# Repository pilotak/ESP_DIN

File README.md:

# ESP8266 DIN mount relay
ESP8266 DIN mount relay *(DPDT@10A and SPST-NO@5A)* board with 433mHz RF receiver or generic input 230VAC or DC (based on jumper and resistor) and temperature sensor (DS18B20 or DHT22). Power supply is good old fashioned style transformer so no noise generated - **radioamateur friendly**. I2C/two pins are accesible on 2.54mm header, for you to extend capabilities.

Board features auto reset with set of GPIO0 LOW when uploading firmware via FTDI so you don't have to press any button to jump into program mode.

## Picture

*Please note that this is picture of v1.0 which in not available in this repo, I have updated the project to v1.1 which fixes some bugs and adds RC filter for relays*

## BOM
### Minimal components

| Qty | Component | Value | Package |
|:---:| --------- | ----- | ------- |
| 3 | Capacitor | 100n | 0805 |
| 1 | Capacitor | 100uF/16V |  Ø5mm, grid 2.032mm |
| 1 | Capacitor | 1000uF/16V | Ø10mm, grid 5mm |
| 2 | Capacitor | R463I24705001K | 18x5x11mm |
| 1 | Diode bridge | KBP307 | |
| 1 | Shottky diode | BAT54S | SOT23 |
| 2 | Diode | S1B | DO214AC (SMA) |
| 1 | Thermal fuse | 2A/115°C | |
| 1 | Fuse | TE5 500mA | TE5 |
| 1 | DPDT relay | 44.62.9.006.0000 | |
| 1 | SPST-NO relay | HF46F/005-HS1 | |
| 1 | LED | green | 3mm |
| 2 | Resistor | 1K | 0805 |
| 3 | Resistor | 4K7 | 0805 |
| 4 | Resistor | 10K | 0805 |
| 4 | Resistor | 160R | 2010 |
| 1 | Resistor | 820R | 0805 |
| 1 | Varistor | S07K275 | |
| 2 | NPN transistor | BC817 | SOT23 |
| 1 | Transformer | BV-EI-305-2050 EI30-1 | |
| 1 | Wifi module | ESP8266-12 | |
| 1 | LDO regulator | LM1117-3.3 | SOT223 |
| 3 | Screw terminal | KF301-5.08-2P | |
| 1 | Screw terminal | KF301-5.08-3P | |
| 1 | Screw terminal | KF350-3.5-2P | |
| 1 | Screw terminal | KF350-3.5-3P | |
| 1 | DIN case | Z100J PS | |

### If RF is required

| Qty | Component | Value | Package |
|:---:| --------- | ----- | ------- |
| 1 | RF reciever | RXB6 | |
| 1 | Capacitor | 100n | 0805 |
| 1 | Capacitor | 0.47uF | SMA |
| 1 | Capacitor | 10uF | SMA |
| 1 | Antenna conenctor | | SMA or u.fl connector |

### If IN is required

| Qty | Component | Value | Package |
|:---:| --------- | ----- | ------- |
| 1 | Diode | SL1M | SOD123 |
| 1 | Opto-coupler | TLP185 | SOP04 |
| 1 | Resistor | 0R | 2010 |
| 1 | Resistor | 200K | 2010 |
| 1 | Resistor | 10K | 0805 |
| 1 | Capacitor | 100n | 0805 |
| 1 | Capacitor | 100uF/16V |  Ø5mm, grid 2.032mm |

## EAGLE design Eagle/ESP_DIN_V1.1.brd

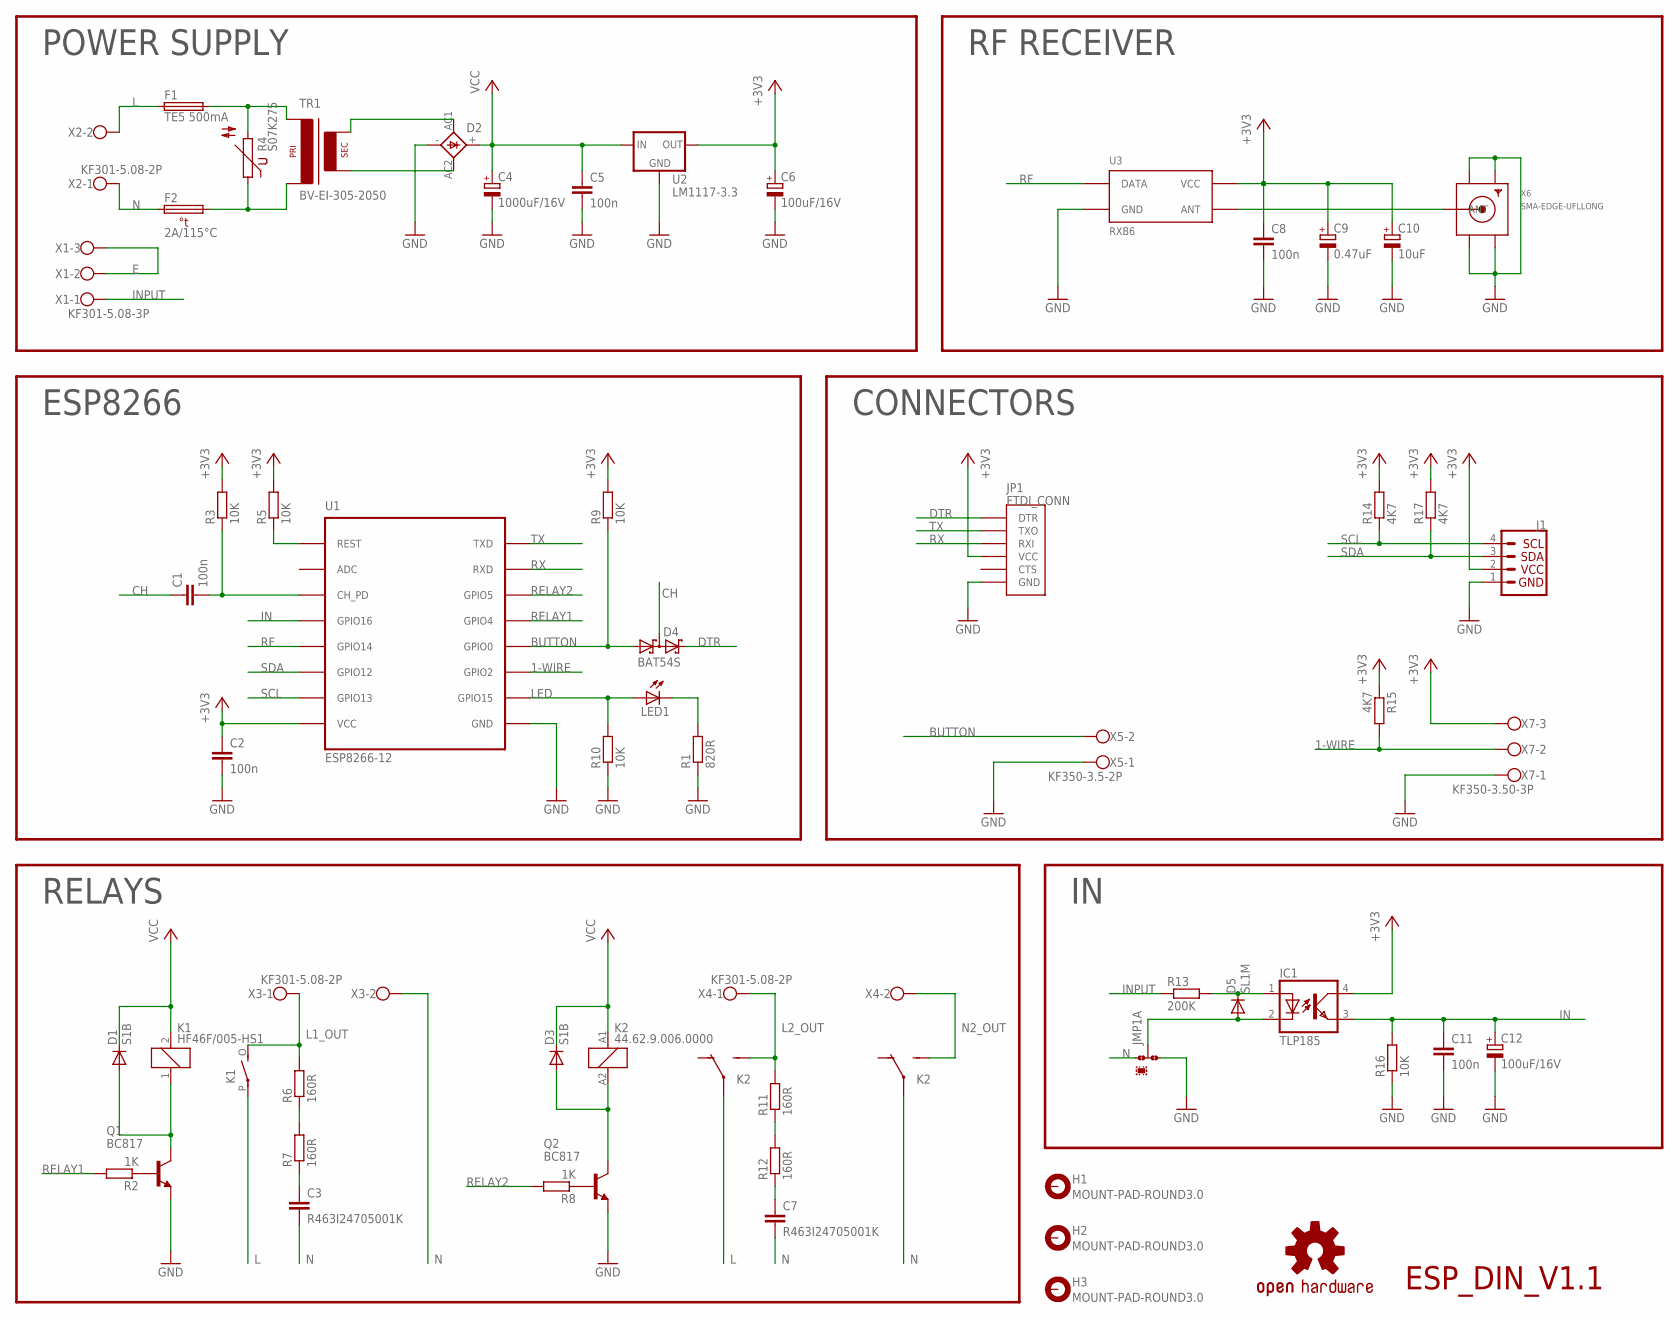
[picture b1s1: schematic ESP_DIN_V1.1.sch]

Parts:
C1, C2, C5, C8, C11: 100n; C0805
C3, C7: R463I24705001K; C150-084X183
C4: 1000uF/16V; TT5D10
C6, C12: 100uF/16V; E2-5
C9: 0.47uF; SMC_A
C10: 10uF; SMC_A
D1, D3: S1B; DO214AC
D2: KBP307
D4: BAT54S; SOT23
D5: SL1M; SOD123
F1: TE5 500mA; TE5
F2: 2A/115°C; THERMAL_6.35
H1, H2, H3: MOUNT-PAD-ROUND3.0; 3,0-PAD
IC1: TLP185; SOP04
J1: I2C_STANDARD_NO_SILK; 1X04_NO_SILK
JMP1: JUMPER-0R-2010-A
JP1: FTDI_CONN; FTDI
K1: HF46F/005-HS1; HF46F
K2: 44.62.9.006.0000; 44.52
LED1: LED3MM
LOGO1: OSHW-LOGOM-COPPER; OSHW-LOGO-M_COPPER
Q1, Q2: BC817; SOT23-BEC
R1: 820R; R0805
R2, R8: 1K; R0805
R3, R5, R9, R10, R16: 10K; R0805
R4: S07K275; S07K250
R6, R7, R11, R12: 160R; R2010
R13: 200K; R2010
R14, R15, R17: 4K7; R0805
TR1: BV-EI-305-2050; EI30-1
U1: ESP8266-12; ESP-12
U2: LM1117-3.3; SOT223
U3: RXB6
X1: KF301-5.08-3P
X2, X3, X4: KF301-5.08-2P
X5: KF350-3.5-2P; KF350-3.50-2P
X6: SMA-EDGE-UFLLONG; SMA_EDGE_UFL_W
X7: KF350-3.50-3P

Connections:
1-WIRE: R15.2, U1.GPIO2, X7.2
+3V3: C2.1, C6.+, C8.1, C9.+, C10.+, IC1.4 (COL), J1.2, JP1.P$4 (VCC), R3.2, R5.2, R9.2, R14.2, R15.1, R17.2, U1.VCC, U2.2 (OUT), U2.4 (OUT), U3.VCC, U3.VCC@1 (VCC), X7.3
ANT: U3.ANT, X6.P (ANT)
BUTTON: D4.1 (A1), R9.1, U1.GPIO0, X5.2
CH: C1.1, D4.3 (C1A2)
DTR: D4.2 (C2), JP1.P$1 (DTR)
E: X1.2, X1.3
GND: C2.2, C4.-, C5.2, C6.-, C8.2, C9.-, C10.-, C11.2, C12.-, D2.-, J1.1, JMP1.3, JP1.P$6 (GND), Q1.E, Q2.E, R1.1, R10.1, R16.1, U1.GND, U2.1 (GND), U3.GND, U3.GND@1 (GND), U3.GND@2 (GND), X5.1, X6.GND@1 (GND1), X6.GND@2 (GND2), X6.GND@3 (GND3), X6.GND@4 (GND4), X7.1
IN: C11.1, C12.+, IC1.3 (EMIT), R16.2, U1.GPIO16
INPUT: R13.1, X1.1
K1_POLE1: D1.A, K1.1, Q1.C
K2_POLE1: D3.A, K2.A2 (2), Q2.C
L: F1.1, K1.P, K2.11, X2.2
L1_OUT: K1.O (NO), R6.2, X3.1
L2_OUT: K2.14 (NO), R11.2, X4.1
LED: LED1.A, R10.2, U1.GPIO15
N: C3.2, C7.2, F2.1, JMP1.1, K2.21, X2.1, X3.2
N2_OUT: K2.24 (NO), X4.2
unnamed: Q2.B, R8.1
unnamed: D2.AC1, TR1.9 (S4)
unnamed: D2.AC2, TR1.7 (S3)
unnamed: LED1.K (C), R1.2
unnamed: D5.A, IC1.2 (C), JMP1.2
unnamed: D5.C, IC1.1 (A), R13.2
unnamed: F1.2, R4.2, TR1.1
unnamed: C3.1, R7.1
unnamed: R5.1, U1.REST
unnamed: C1.2, R3.1, U1.CH_PD
unnamed: R6.1, R7.2
unnamed: C7.1, R12.1
unnamed: F2.2, R4.1, TR1.5 (P2)
unnamed: R11.1, R12.2
unnamed: Q1.B, R2.1
RELAY1: R2.2, U1.GPIO5 (GPIO4)
RELAY2: R8.2, U1.GPIO4 (GPIO5)
RF: U1.GPIO14, U3.DATA
RX: JP1.P$3 (RXI), U1.RXD
SCL: J1.4, R14.1, U1.GPIO13
SDA: J1.3, R17.1, U1.GPIO12
TX: JP1.P$2 (TXO), U1.TXD
VCC: C4.+, C5.1, D1.C, D2.+, D3.C, K1.2, K2.A1 (1), U2.3 (IN)

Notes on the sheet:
POWER SUPPLY
ESP8266
RELAYS
CONNECTORS
RF RECEIVER
ESP_DIN_V1.1

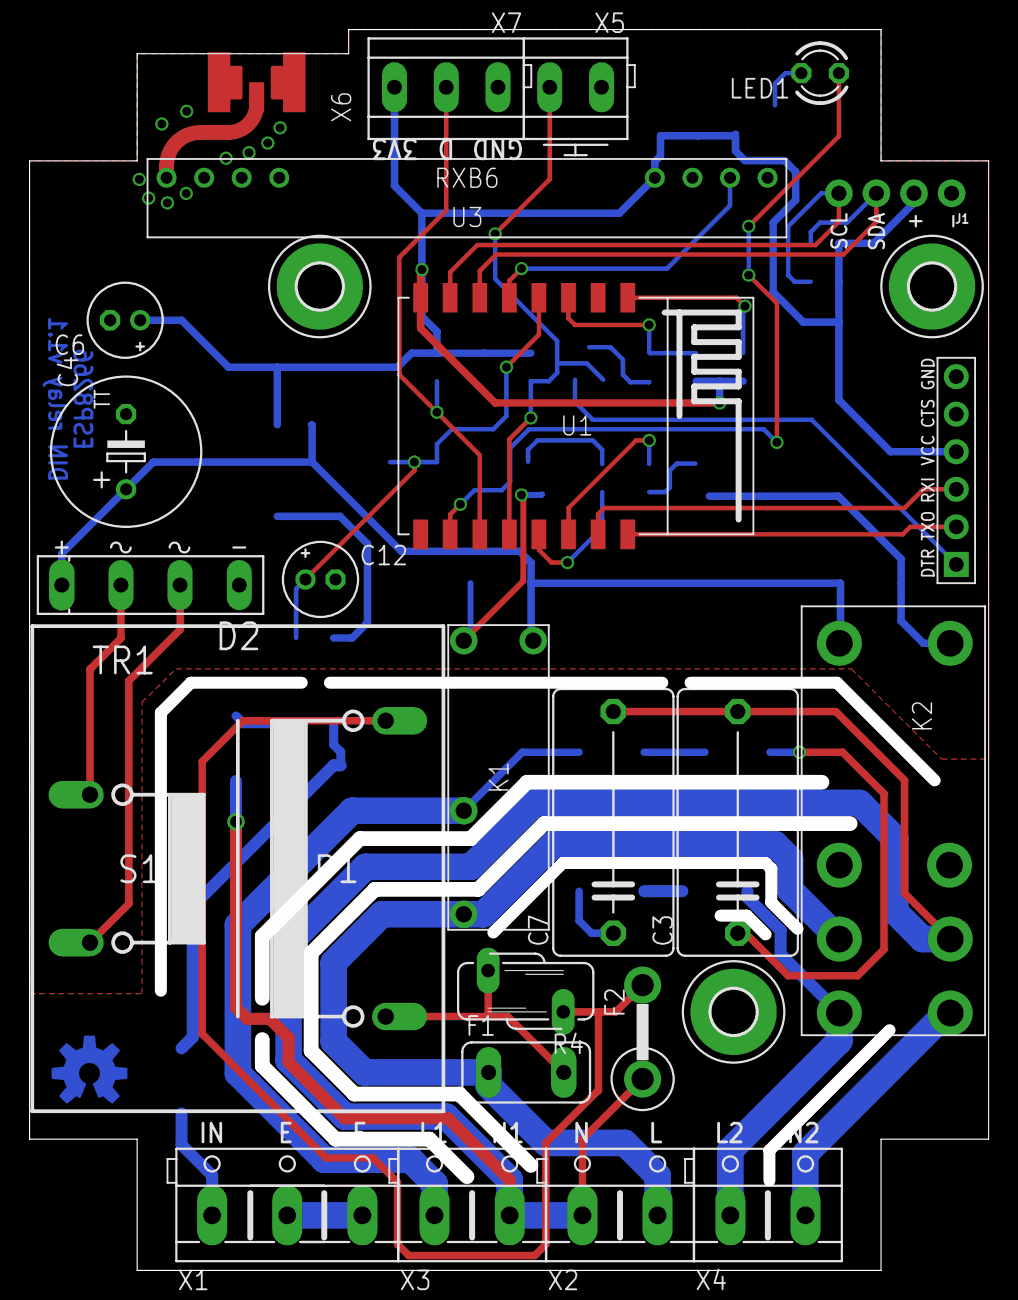
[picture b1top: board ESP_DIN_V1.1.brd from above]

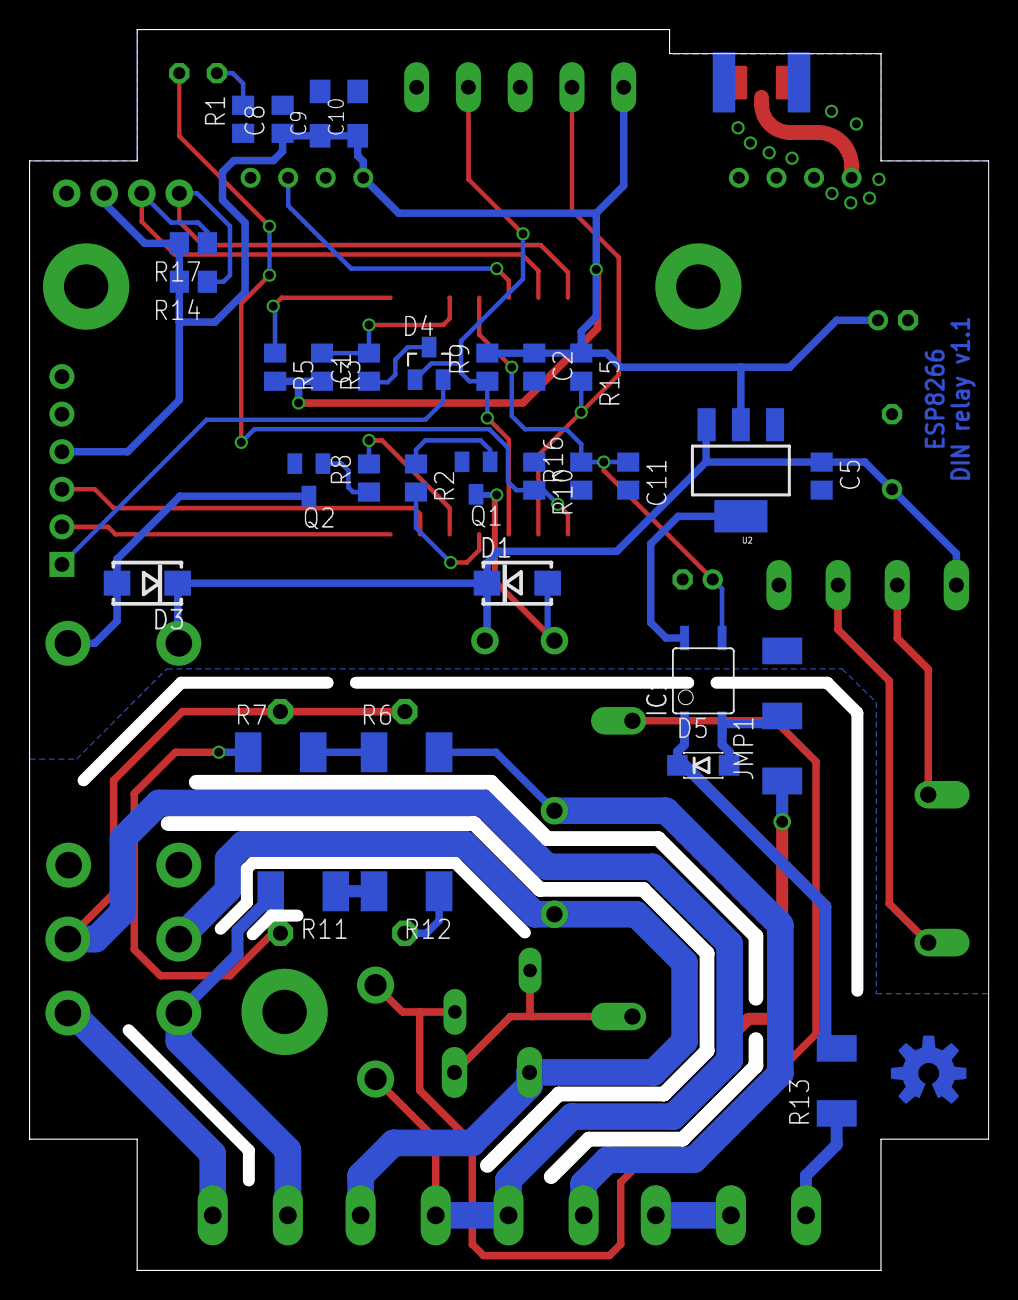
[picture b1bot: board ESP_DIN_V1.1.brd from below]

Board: 2 copper layers, 63.9 x 82.9 mm, 60 parts (33 on the bottom side), 41 nets.

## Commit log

2018-04-27 eagle files
2018-05-05 readme + optocoupler fix
2018-05-05 readme update
2018-05-05 picture
2018-05-05 jpg fix
2018-05-05 notice
2018-05-07 milling corrections
2018-05-16 IN & RF together

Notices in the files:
parts and their libraries:
SparkFun-Connectors: Licensing: Creative Commons ShareAlike 4.0 International - https://creativecommons.org/licenses/by-sa/4.0
